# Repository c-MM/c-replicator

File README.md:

# c-replicator
stuff for the second c-replicator

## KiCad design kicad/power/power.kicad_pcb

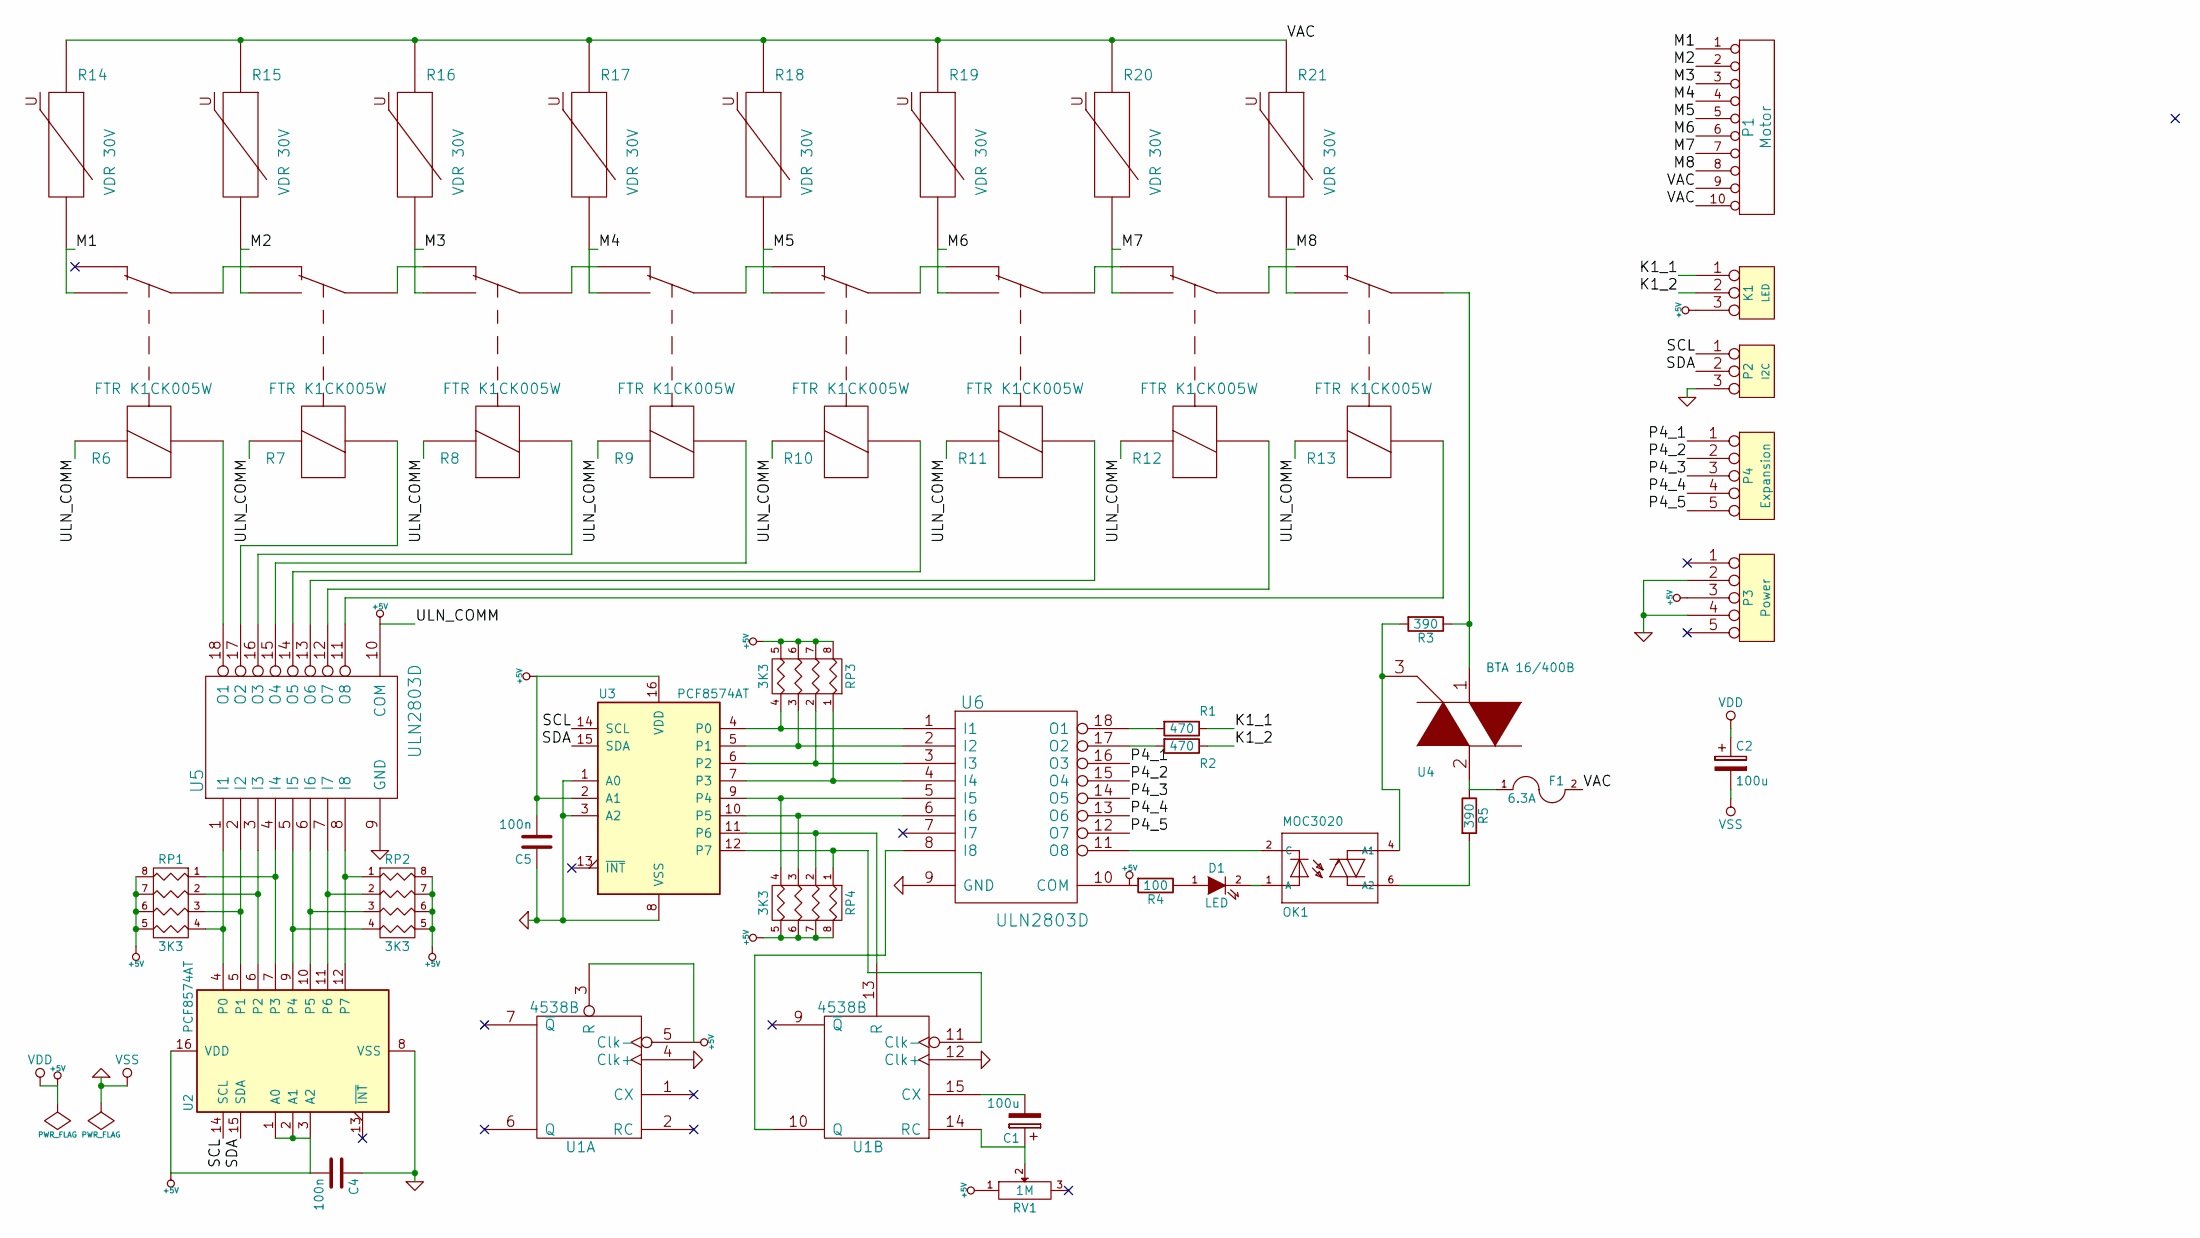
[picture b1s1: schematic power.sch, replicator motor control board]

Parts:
C1, C2: 100u; c_elec_6.3x5.8
C4, C5: 100n; C_0603_HandSoldering
D1: LED; LED-5MM
F1: 6.3A; Fuse_5mm
K1: LED; PSS254-3G
OK1: MOC3020; MOC_3020
P1: Motor; Akl_Ria_230_10
P2: I2C; PSS254-3G
P3: Power; PSS254-5G
P4: Expansion; PSS254-5G
R1, R2: 470; R_0603_HandSoldering
R3, R5: 390; R_0603_HandSoldering
R4: 100; R_0603_HandSoldering
R6, R7, R8, R9, R10, R11, R12, R13: FTR K1CK005W; Relais_1X
R14, R15, R16, R17, R18, R19, R20, R21: VDR 30V; R_1206_HandSoldering
RP1, RP2, RP3, RP4: 3K3; R_Array_Convex_4x1206
RV1: 1M; Potentiometer_Bourns_3296W_3-8Zoll_Inline_ScrewUp
U1: 4538B; SO-16-N
U2, U3: PCF8574AT; SOIC-16_7.5x10.3mm_Pitch1.27mm
U4: BTA 16/400B; TO220_VERT
U5, U6: ULN2803D; SOIC-18_7.5x11.6mm_Pitch1.27mm

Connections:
+5V: C2.1, C4.2, C5.2, K1.3, P3.3, R4.2, R6.1 (Spule_A), R7.1 (Spule_A), R8.1 (Spule_A), R9.1 (Spule_A), R10.1 (Spule_A), R11.1 (Spule_A), R12.1 (Spule_A), R13.1 (Spule_A), RP1.5 (R4), RP1.6 (R3), RP1.7 (R2), RP1.8 (R1), RP2.5 (R4), RP2.6 (R3), RP2.7 (R2), RP2.8 (R1), RP3.5 (R4), RP3.6 (R3), RP3.7 (R2), RP3.8 (R1), RP4.5 (R4), RP4.6 (R3), RP4.7 (R2), RP4.8 (R1), RV1.1, U1.3 (R), U1.5 (Clk-), U1.16 (VDD), U2.1 (A0), U2.2 (A1), U2.3 (A2), U2.16 (VDD), U3.2 (A1), U3.16 (VDD), U5.10 (COM), U6.10 (COM)
/K1_1: K1.1, R1.1
/K1_2: K1.2 (PM), R2.1
/M1: P1.1, R6.2 (NO), R14.2
/M2: P1.2, R7.2 (NO), R15.2
/M3: P1.3, R8.2 (NO), R16.2
/M4: P1.4, R9.2 (NO), R17.2
/M5: P1.5, R10.2 (NO), R18.2
/M6: P1.6, R11.2 (NO), R19.2
/M7: P1.7, R12.2 (NO), R20.2
/M8: P1.8, R13.2 (NO), R21.2
/P4_1: P4.1, U6.16 (O3)
/P4_2: P4.2, U6.15 (O4)
/P4_3: P4.3, U6.14 (O5)
/P4_4: P4.4, U6.13 (O6)
/P4_5: P4.5, U6.12 (O7)
/SCL: P2.1, U2.14 (SCL), U3.14 (SCL)
/SDA: P2.2 (PM), U2.15 (SDA), U3.15 (SDA)
/VAC: F1.2, P1.9, P1.10, R14.1, R15.1, R16.1, R17.1, R18.1, R19.1, R20.1, R21.1
GND: C2.2, C4.1, C5.1, P2.3, P3.2, P3.4, U1.4 (Clk+), U1.8 (VSS), U1.12 (Clk+), U2.8 (VSS), U3.1 (A0), U3.3 (A2), U3.8 (VSS), U5.9 (GND), U6.9 (GND)
unnamed: C1.1, RV1.2, U1.14 (RC)
unnamed: C1.2, U1.15 (CX)
unnamed: D1.1 (A), R4.1
unnamed: D1.2 (K), OK1.1 (A)
unnamed: F1.1, R5.1, U4.2
unnamed: OK1.2 (C), U6.11 (O8)
unnamed: OK1.4 (A1), R3.2, U4.3
unnamed: OK1.6 (A2), R5.2
unnamed: R1.2, U6.18 (O1)
unnamed: R2.2, U6.17 (O2)
unnamed: R6.3 (Spule_B), U5.18 (O1)
unnamed: R6.5 (C), R7.4 (NC)
unnamed: R7.3 (Spule_B), U5.17 (O2)
unnamed: R7.5 (C), R8.4 (NC)
unnamed: R8.3 (Spule_B), U5.16 (O3)
unnamed: R8.5 (C), R9.4 (NC)
unnamed: R9.3 (Spule_B), U5.15 (O4)
unnamed: R10.3 (Spule_B), U5.14 (O5)
unnamed: R9.5 (C), R10.4 (NC)
unnamed: R10.5 (C), R11.4 (NC)
unnamed: R11.3 (Spule_B), U5.13 (O6)
unnamed: R11.5 (C), R12.4 (NC)
unnamed: R12.3 (Spule_B), U5.12 (O7)
unnamed: R12.5 (C), R13.4 (NC)
unnamed: R13.3 (Spule_B), U5.11 (O8)
unnamed: R3.1, R13.5 (C), U4.1
unnamed: RP1.1, U2.7 (P3), U5.4 (I4)
unnamed: RP1.2, U2.6 (P2), U5.3 (I3)
unnamed: RP1.3, U2.5 (P1), U5.2 (I2)
unnamed: RP1.4, U2.4 (P0), U5.1 (I1)
unnamed: RP2.1, U2.12 (P7), U5.8 (I8)
unnamed: RP2.2, U2.11 (P6), U5.7 (I7)
unnamed: RP2.3, U2.10 (P5), U5.6 (I6)
unnamed: RP2.4, U2.9 (P4), U5.5 (I5)
unnamed: RP3.1, U3.7 (P3), U6.4 (I4)
unnamed: RP3.2, U3.6 (P2), U6.3 (I3)
unnamed: RP3.3, U3.5 (P1), U6.2 (I2)
unnamed: RP3.4, U3.4 (P0), U6.1 (I1)
unnamed: RP4.1, U1.11 (Clk-), U3.12 (P7)
unnamed: RP4.2, U1.13 (R), U3.11 (P6)
unnamed: RP4.3, U3.10 (P5), U6.6 (I6)
unnamed: RP4.4, U3.9 (P4), U6.5 (I5)
unnamed: U1.10 (Q), U6.8 (I8)

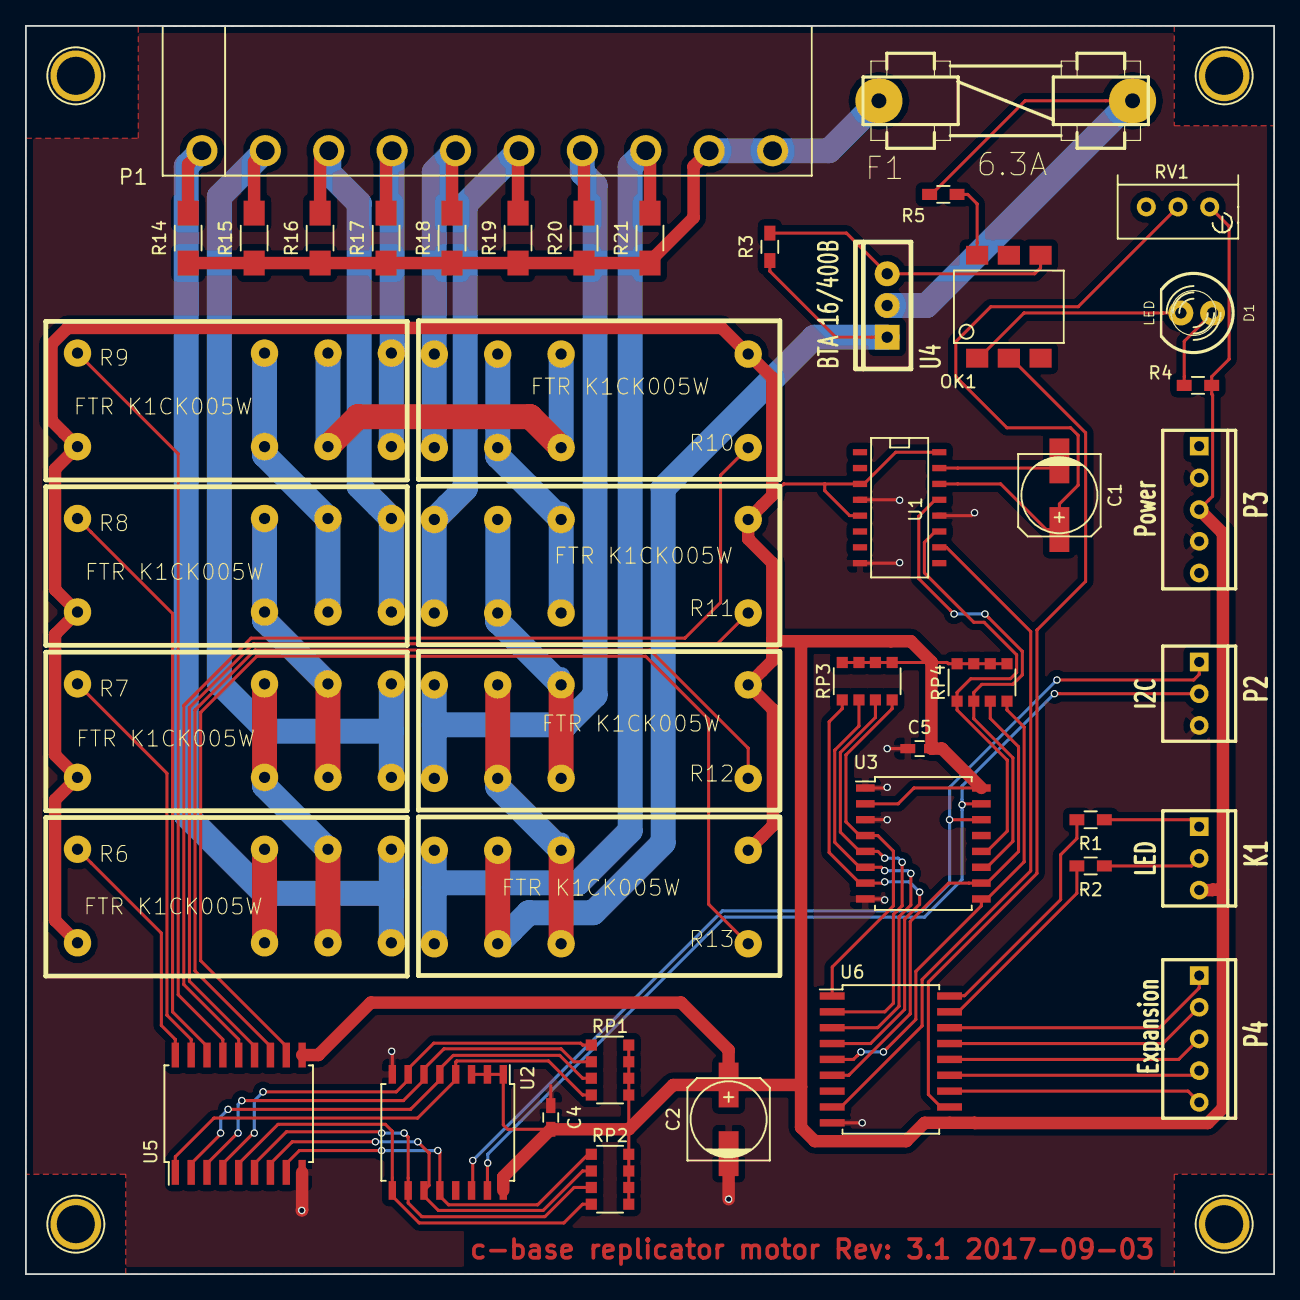
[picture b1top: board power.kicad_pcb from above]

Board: 2 copper layers, 100.0 x 100.0 mm, 44 parts (0 on the bottom side), 63 nets.

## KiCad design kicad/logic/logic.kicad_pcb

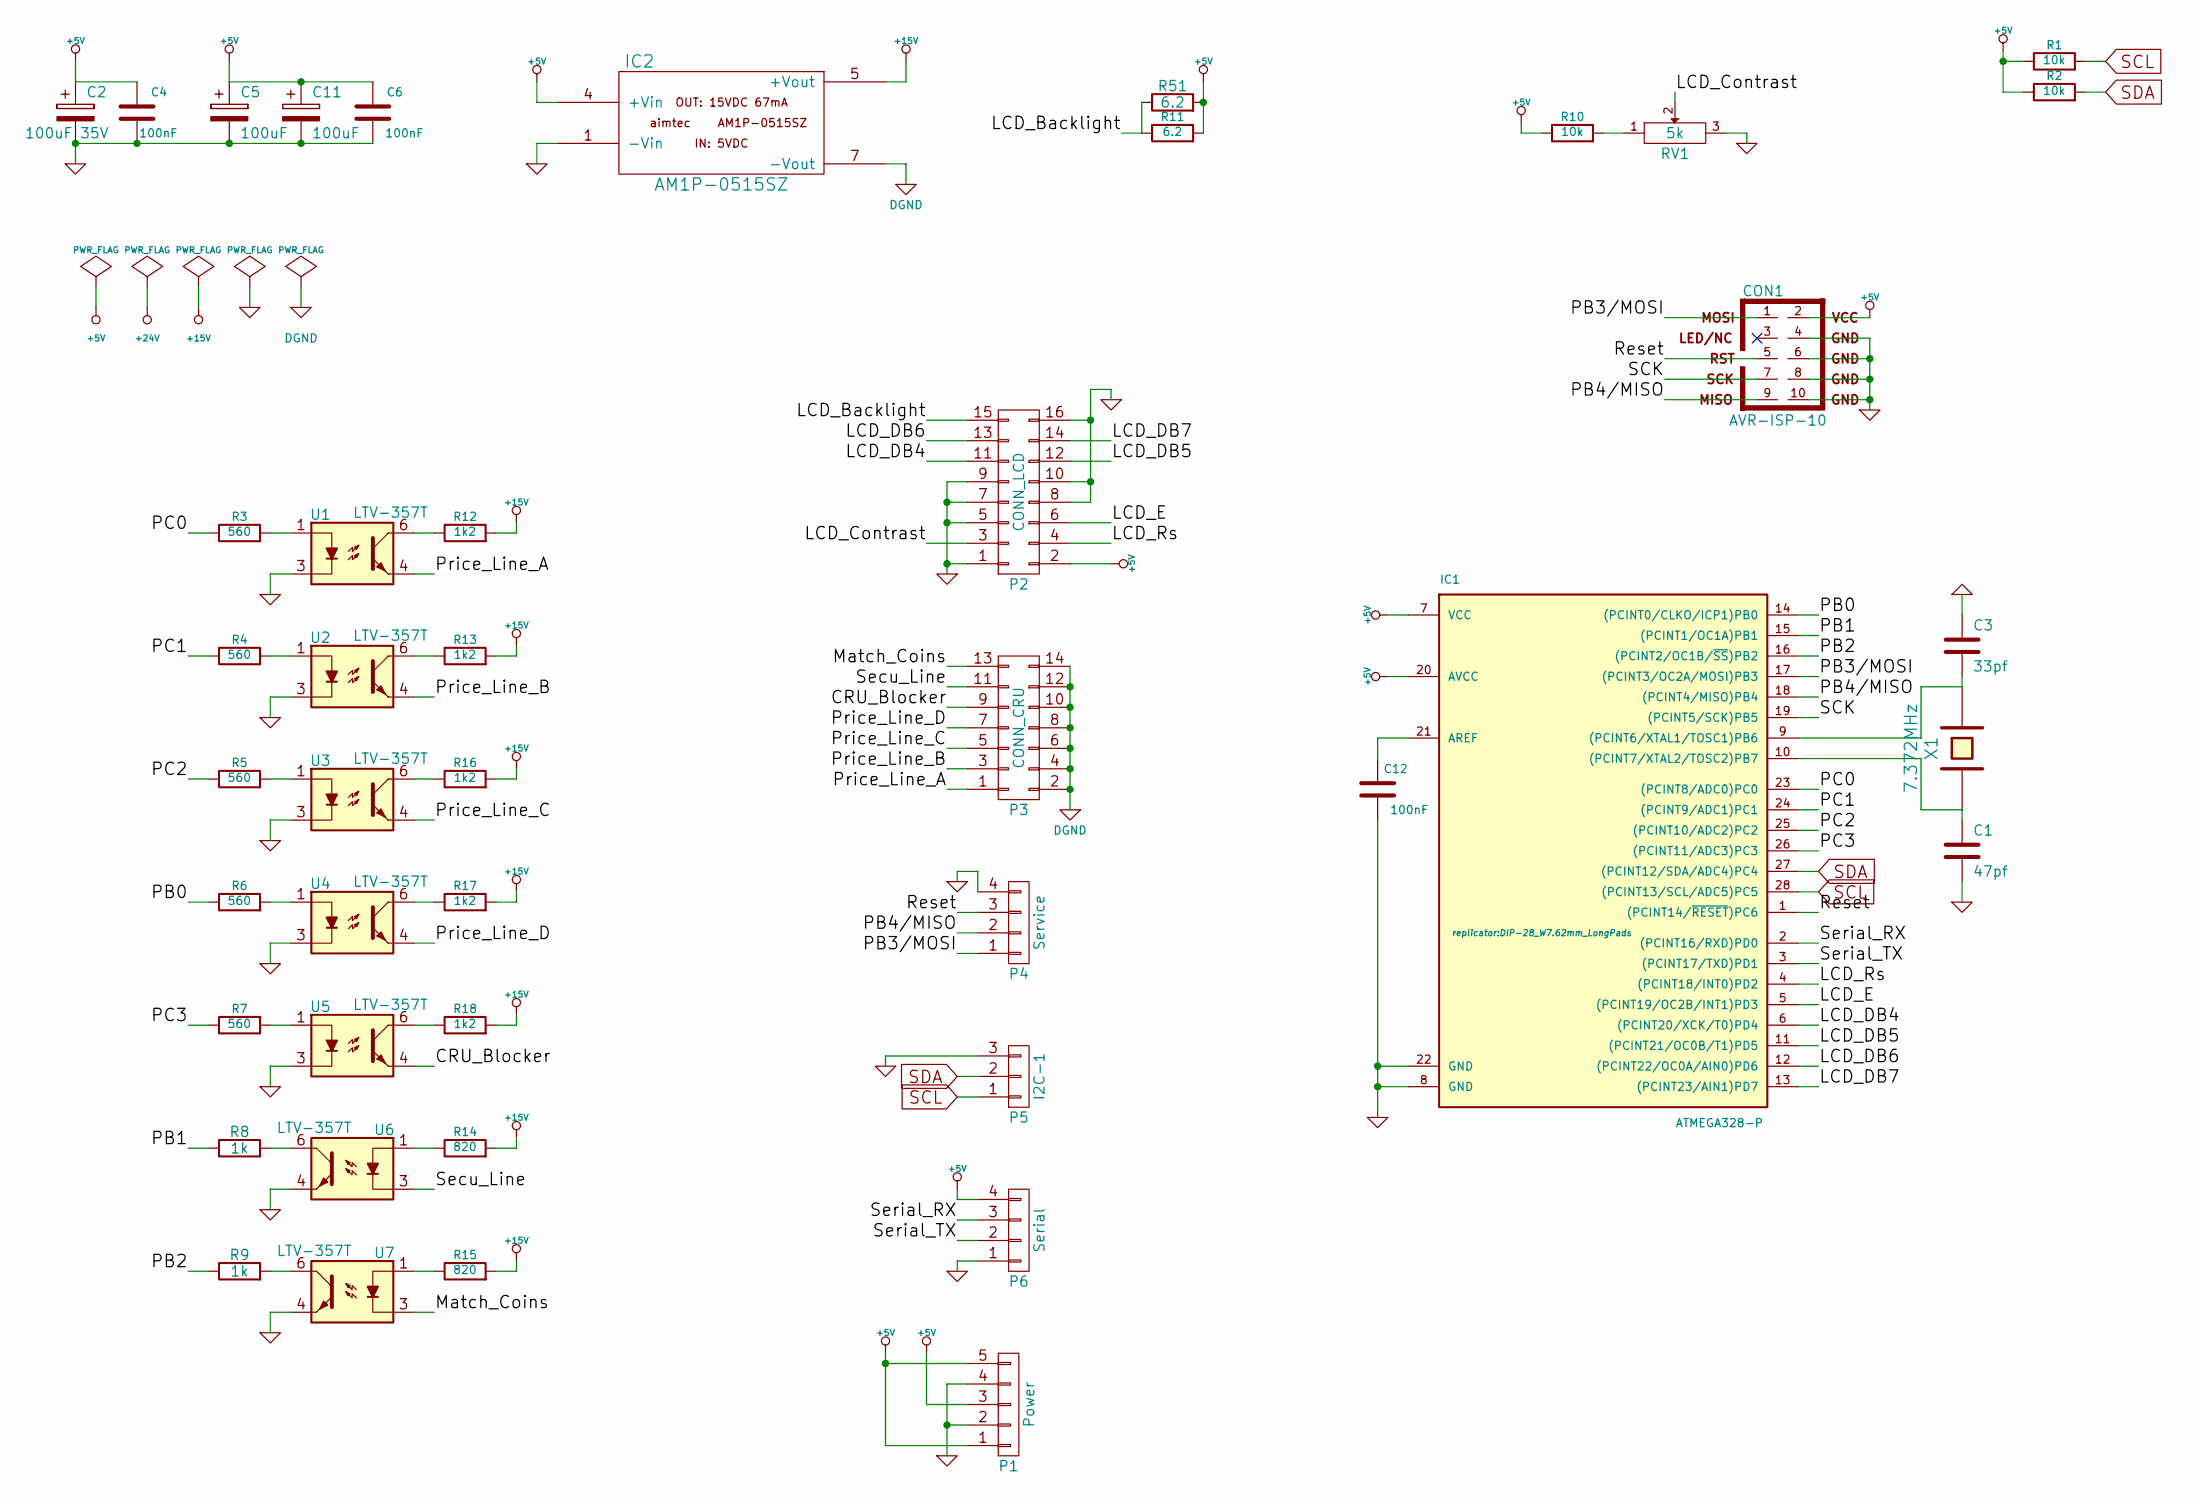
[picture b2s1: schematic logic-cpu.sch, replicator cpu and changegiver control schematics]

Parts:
C1: 47pf; C_0603_HandSoldering
C2: 100uF 35V; c_elec_6.3x7.7
C3: 33pf; C_0603_HandSoldering
C4, C6, C12: 100nF; C_0603_HandSoldering
C5, C11: 100uF; c_elec_6.3x5.8
CON1: AVR-ISP-10; IDC_Header_Straight_10pins
IC1: ATMEGA328-P; DIP-28_W7.62mm_LongPads
IC2: AM1P-0515SZ; DIP-8_W7.62mm_LongPads
P1: Power; PSS254-5G
P2: CONN_LCD; IDC_Header_Straight_16pins
P3: CONN_CRU; IDC_Header_Straight_14pins
P4: Service; PSS254-4G
P5: I2C-1; PSS254-3G
P6: Serial; PSS254-4G
R1, R2, R10: 10k; R_0603_HandSoldering
R3, R4, R5, R6, R7: 560; R_0603_HandSoldering
R8, R9: 1k; R_0603_HandSoldering
R11, R51: 6.2; R_1206_HandSoldering
R12, R13, R16, R17, R18: 1k2; R_1206_HandSoldering
R14, R15: 820; R_1206_HandSoldering
RV1: 5k; Potentiometer_Trimmer-Suntan-TSR-3386P
U1, U2, U3, U4, U5, U6, U7: LTV-357T; Optocoupler_SMD_HandSoldering_KPC357_LTV35x_PC357_SingleCha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
X1: 7.372MHz; Crystal_HC49-U_Vertical

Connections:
+15V: IC2.5 (+Vout), R12.2, R13.2, R14.2, R15.2, R16.2, R17.2, R18.2
/cpu/CRU_Blocker: P3.9, U5.4
/cpu/LCD_Backlight: P2.15, R11.1, R51.1
/cpu/LCD_Contrast: P2.3, RV1.2
/cpu/LCD_DB4: IC1.6 ((PCINT20/XCK/T0)PD4), P2.11
/cpu/LCD_DB5: IC1.11 ((PCINT21/OC0B/T1)PD5), P2.12
/cpu/LCD_DB6: IC1.12 ((PCINT22/OC0A/AIN0)PD6), P2.13
/cpu/LCD_DB7: IC1.13 ((PCINT23/AIN1)PD7), P2.14
/cpu/LCD_E: IC1.5 ((PCINT19/OC2B/INT1)PD3), P2.6
/cpu/LCD_Rs: IC1.4 ((PCINT18/INT0)PD2), P2.4
/cpu/Match_Coins: P3.13, U7.3
/cpu/PB0: IC1.14 ((PCINT0/CLKO/ICP1)PB0), R6.1
/cpu/PB1: IC1.15 ((PCINT1/OC1A)PB1), R8.1
/cpu/PB2: IC1.16 ((PCINT2/OC1B/~SS~)PB2), R9.1
/cpu/PB3/MOSI: CON1.1, IC1.17 ((PCINT3/OC2A/MOSI)PB3), P4.1
/cpu/PB4/MISO: CON1.9, IC1.18 ((PCINT4/MISO)PB4), P4.2
/cpu/PC0: IC1.23 ((PCINT8/ADC0)PC0), R3.1
/cpu/PC1: IC1.24 ((PCINT9/ADC1)PC1), R4.1
/cpu/PC2: IC1.25 ((PCINT10/ADC2)PC2), R5.1
/cpu/PC3: IC1.26 ((PCINT11/ADC3)PC3), R7.1
/cpu/Price_Line_A: P3.1, U1.4
/cpu/Price_Line_B: P3.3, U2.4
/cpu/Price_Line_C: P3.5, U3.4
/cpu/Price_Line_D: P3.7, U4.4
/cpu/Reset: CON1.5, IC1.1 ((PCINT14/~RESET~)PC6), P4.3
/cpu/SCK: CON1.7, IC1.19 ((PCINT5/SCK)PB5)
/cpu/Secu_Line: P3.11, U6.3
/cpu/Serial_RX: IC1.2 ((PCINT16/RXD)PD0), P6.3
/cpu/Serial_TX: IC1.3 ((PCINT17/TXD)PD1), P6.2
DGND: IC2.7 (-Vout), P3.2, P3.4, P3.6, P3.8, P3.10, P3.12, P3.14
unnamed: C1.1, IC1.10 ((PCINT7/XTAL2/TOSC2)PB7), X1.2
unnamed: C3.2, IC1.9 ((PCINT6/XTAL1/TOSC1)PB6), X1.1
unnamed: C12.2, IC1.21 (AREF)
unnamed: R3.2, U1.1
unnamed: R4.2, U2.1
unnamed: R5.2, U3.1
unnamed: R6.2, U4.1
unnamed: R7.2, U5.1
unnamed: R8.2, U6.6
unnamed: R9.2, U7.6
unnamed: R10.2, RV1.1
unnamed: R12.1, U1.6
unnamed: R13.1, U2.6
unnamed: R14.1, U6.1
unnamed: R15.1, U7.1
unnamed: R16.1, U3.6
unnamed: R17.1, U4.6
unnamed: R18.1, U5.6
SDA: IC1.27 ((PCINT12/SDA/ADC4)PC4), P5.2, R2.2; also elsewhere on the board

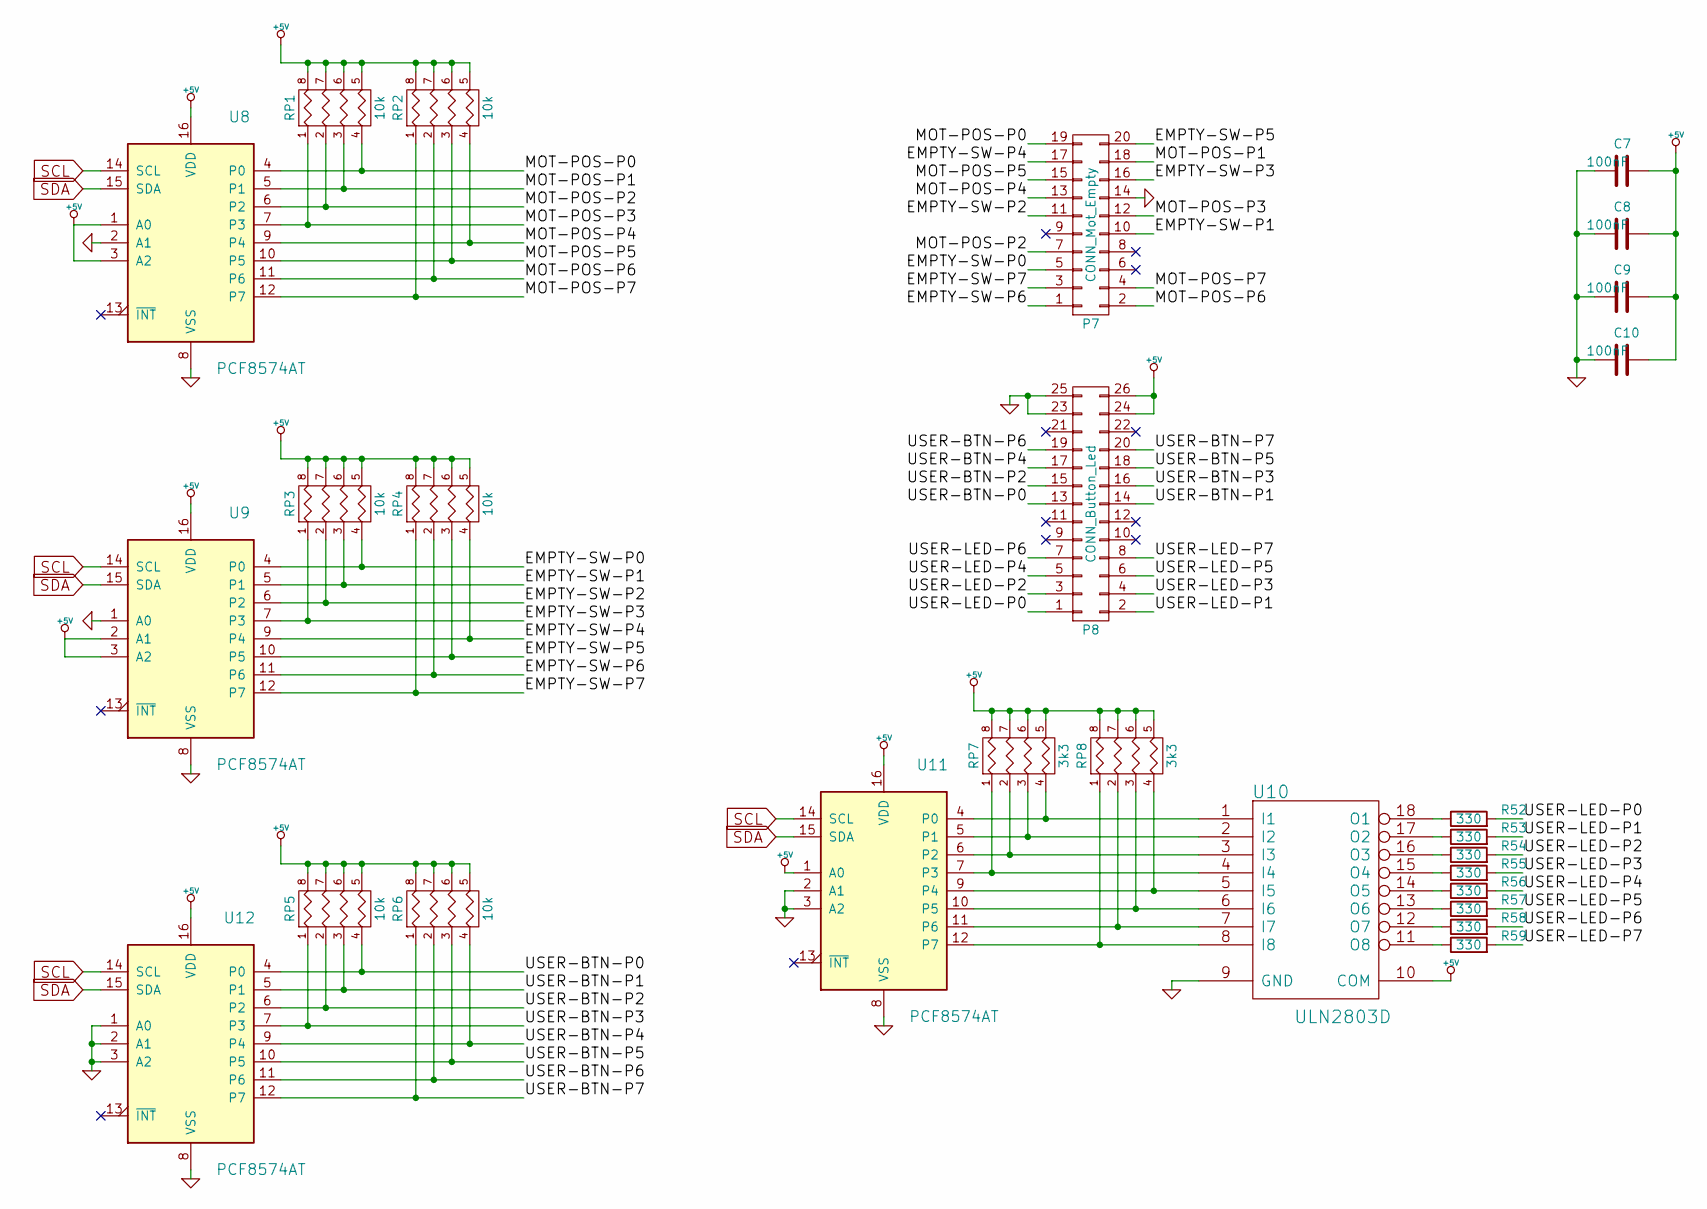
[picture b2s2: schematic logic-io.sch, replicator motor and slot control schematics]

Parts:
C7, C8, C9, C10: 100nF; C_0603_HandSoldering
P7: CONN_Mot_Empty; IDC_Header_Straight_20pins
P8: CONN_Button_Led; IDC_Header_Straight_26pins
R52, R53, R54, R55, R56, R57, R58, R59: 330; R_0603_HandSoldering
RP1, RP2, RP3, RP4, RP5, RP6: 10k; R_Array_Convex_4x1206
RP7, RP8: 3k3; R_Array_Convex_4x1206
U8, U9, U11, U12: PCF8574AT; SOIC-16_7.5x10.3mm_Pitch1.27mm
U10: ULN2803D; SOIC-18_7.5x11.6mm_Pitch1.27mm

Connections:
/io/EMPTY-SW-P0: P7.5, RP3.4, U9.4 (P0)
/io/EMPTY-SW-P1: P7.10, RP3.3, U9.5 (P1)
/io/EMPTY-SW-P2: P7.11, RP3.2, U9.6 (P2)
/io/EMPTY-SW-P3: P7.16, RP3.1, U9.7 (P3)
/io/EMPTY-SW-P4: P7.17, RP4.4, U9.9 (P4)
/io/EMPTY-SW-P5: P7.20, RP4.3, U9.10 (P5)
/io/EMPTY-SW-P6: P7.1, RP4.2, U9.11 (P6)
/io/EMPTY-SW-P7: P7.3, RP4.1, U9.12 (P7)
/io/MOT-POS-P0: P7.19, RP1.4, U8.4 (P0)
/io/MOT-POS-P1: P7.18, RP1.3, U8.5 (P1)
/io/MOT-POS-P2: P7.7, RP1.2, U8.6 (P2)
/io/MOT-POS-P3: P7.12, RP1.1, U8.7 (P3)
/io/MOT-POS-P4: P7.13, RP2.4, U8.9 (P4)
/io/MOT-POS-P5: P7.15, RP2.3, U8.10 (P5)
/io/MOT-POS-P6: P7.2, RP2.2, U8.11 (P6)
/io/MOT-POS-P7: P7.4, RP2.1, U8.12 (P7)
/io/USER-BTN-P0: P8.13, RP5.4, U12.4 (P0)
/io/USER-BTN-P1: P8.14, RP5.3, U12.5 (P1)
/io/USER-BTN-P2: P8.15, RP5.2, U12.6 (P2)
/io/USER-BTN-P3: P8.16, RP5.1, U12.7 (P3)
/io/USER-BTN-P4: P8.17, RP6.4, U12.9 (P4)
/io/USER-BTN-P5: P8.18, RP6.3, U12.10 (P5)
/io/USER-BTN-P6: P8.19, RP6.2, U12.11 (P6)
/io/USER-BTN-P7: P8.20, RP6.1, U12.12 (P7)
/io/USER-LED-P0: P8.1, R52.2
/io/USER-LED-P1: P8.2, R53.2
/io/USER-LED-P2: P8.3, R54.2
/io/USER-LED-P3: P8.4, R55.2
/io/USER-LED-P4: P8.5, R56.2
/io/USER-LED-P5: P8.6, R57.2
/io/USER-LED-P6: P8.7, R58.2
/io/USER-LED-P7: P8.8, R59.2
unnamed: R52.1, U10.18 (O1)
unnamed: R53.1, U10.17 (O2)
unnamed: R54.1, U10.16 (O3)
unnamed: R55.1, U10.15 (O4)
unnamed: R56.1, U10.14 (O5)
unnamed: R57.1, U10.13 (O6)
unnamed: R58.1, U10.12 (O7)
unnamed: R59.1, U10.11 (O8)
unnamed: RP7.1, U10.4 (I4), U11.7 (P3)
unnamed: RP7.2, U10.3 (I3), U11.6 (P2)
unnamed: RP7.3, U10.2 (I2), U11.5 (P1)
unnamed: RP7.4, U10.1 (I1), U11.4 (P0)
unnamed: RP8.1, U10.8 (I8), U11.12 (P7)
unnamed: RP8.2, U10.7 (I7), U11.11 (P6)
unnamed: RP8.3, U10.6 (I6), U11.10 (P5)
unnamed: RP8.4, U10.5 (I5), U11.9 (P4)
SDA: U8.15 (SDA), U9.15 (SDA), U11.15 (SDA), U12.15 (SDA); also elsewhere on the board

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
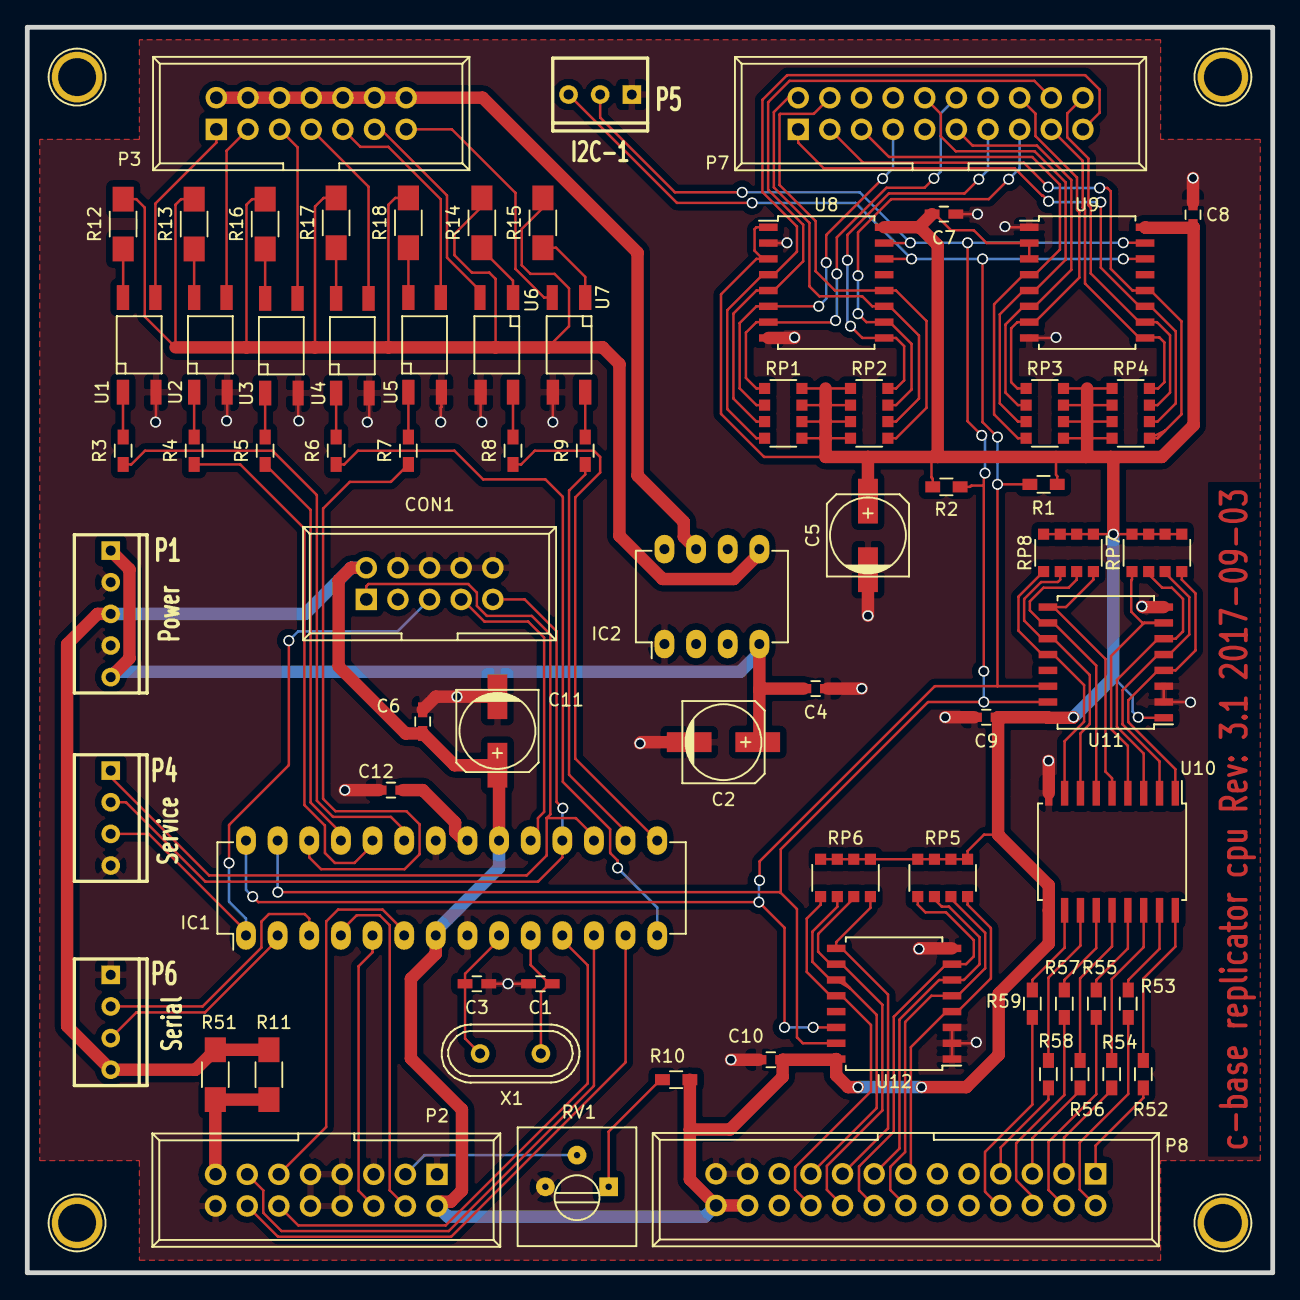
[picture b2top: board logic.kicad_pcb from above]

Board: 2 copper layers, 100.0 x 100.0 mm, 72 parts (0 on the bottom side), 101 nets.

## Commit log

2019-01-20 add prototype for connector panel
2019-01-20 next prototype for connector panel
2019-01-20 add openscad source for connector panel
2019-01-20 add mounting holes
2019-01-20 remove unused tests
2019-01-20 turn make top inforcement for better printing
2019-01-20 make it 4mm smaller
2019-01-26 add openscad and stl for cashbox
2019-01-27 add holder for service buttons
2019-01-30 add kicad files
2019-01-30 add schematics in pdf
2019-01-30 ignore avg-gcc output files
2019-01-30 add firmware for replicator
2019-01-31 add kicad symbol libs and remove *.lib from .gitignore
2019-02-03 add git revision to makefile
2019-02-03 rebuild on version change
2019-02-03 add version display on boot
2019-02-03 add dependency on version
2019-02-03 split version info
2019-02-03 ignore version file
2019-02-03 always use long version
2019-04-06 add Freiausgabe
2019-05-01 invert status logic, send on char less in serial_tx
2019-05-02 revert length fix
2019-05-02 fix status tx length, only count vends when not reseting slots
2019-05-02 add counter reset command, don't increase error counter on too litle credit, show disables slots as blocked ind status command
2019-05-02 add reboot, enable and free dispense commands
2019-05-03 rename 3d-print files
2019-05-03 rename version file to version.h
2019-05-03 create vrsion.h on git changes
2019-05-03 suppress output from cmp
2019-05-03 use version.h
2019-05-04 add comand to dispense slot
